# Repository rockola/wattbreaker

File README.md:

wattbreaker
================

Another silly dual-stage overdrive by Mark Hammer. 
See https://www.diystompboxes.com/smfforum/index.php?topic=126135.0 for more info.

* v0.1: initial revision, unverified

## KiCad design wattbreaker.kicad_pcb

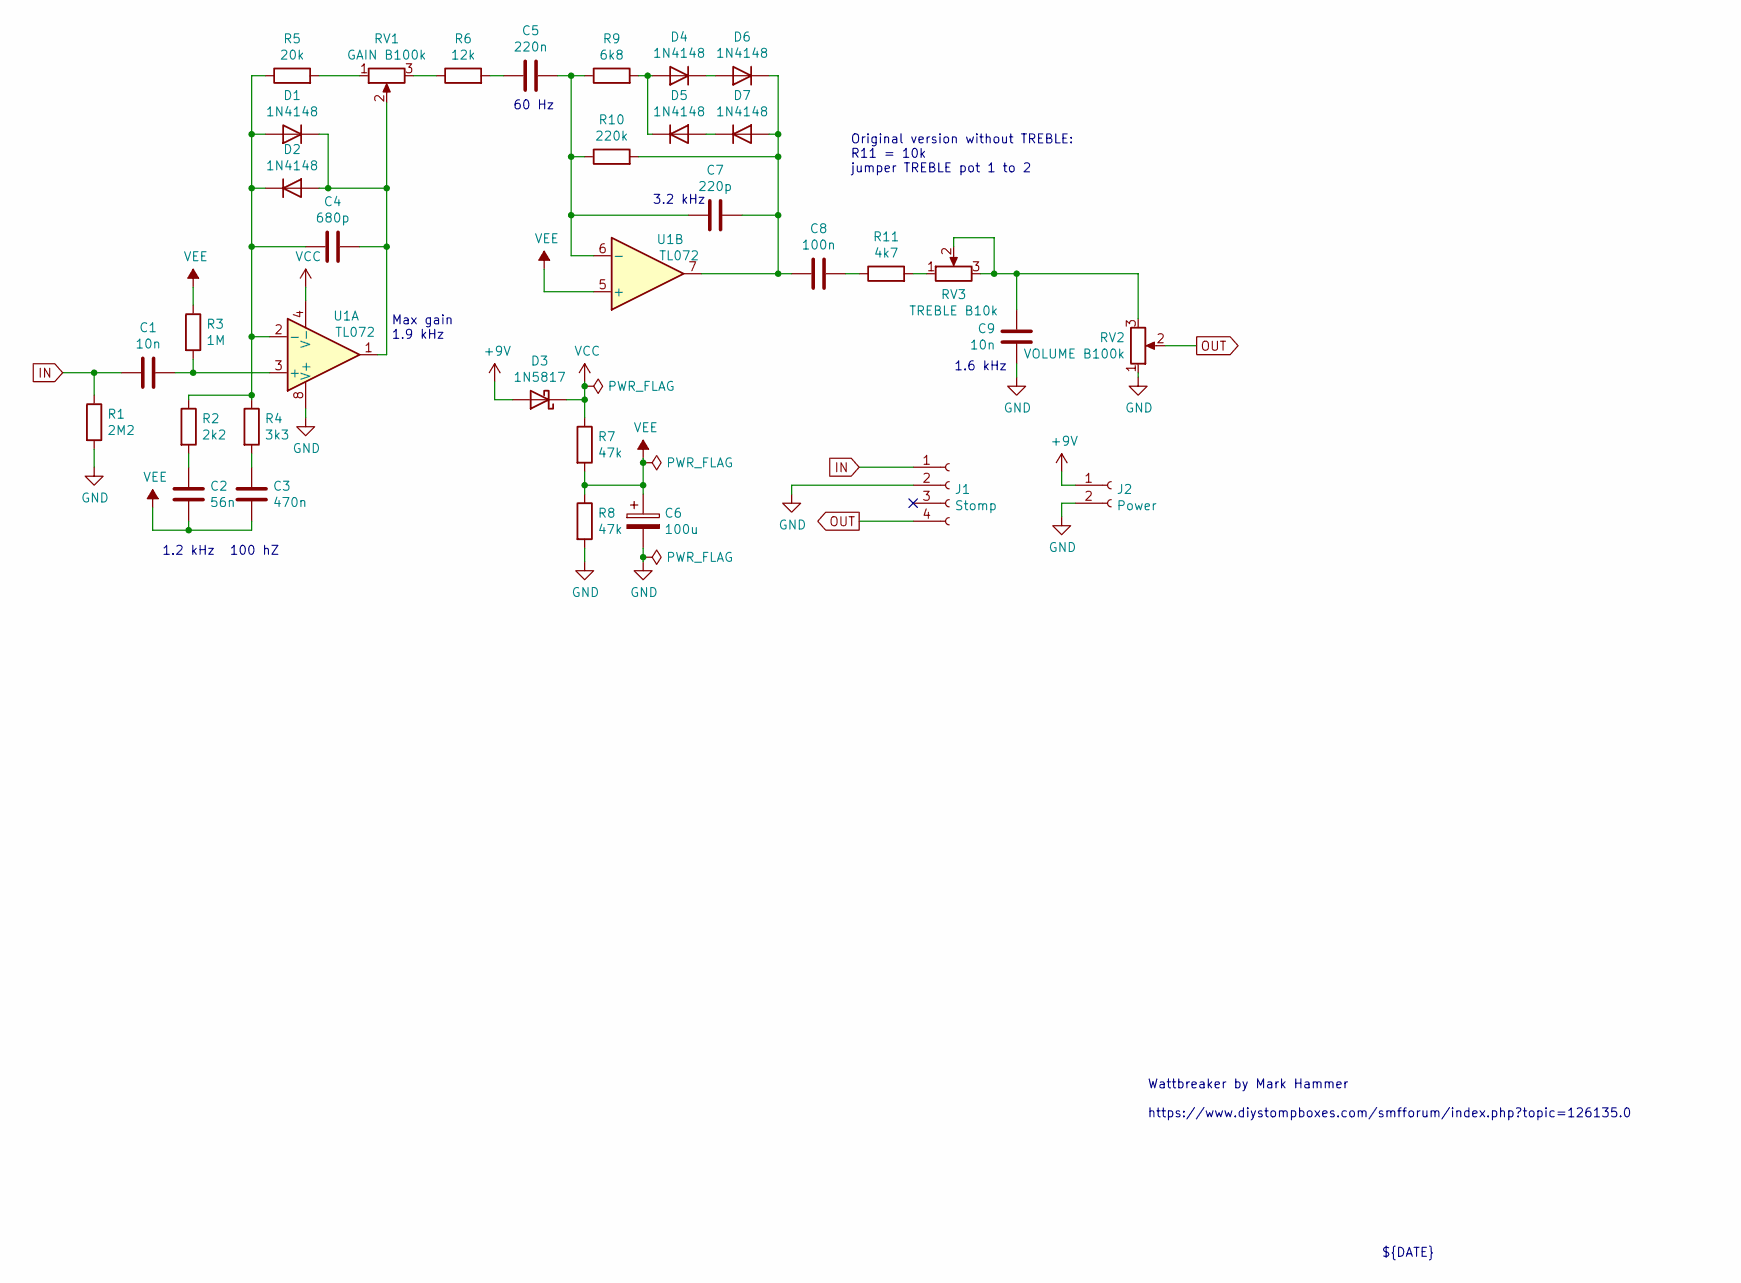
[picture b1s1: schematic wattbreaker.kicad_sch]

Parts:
C1, C9: 10n; C_Box_7.2_2.5
C2: 56n; C_Box_7.2_2.5
C3: 470n; C_Box_7.2_4.5
C4: 680p; C_Box_7.2_2.5
C5: 220n; C_Box_7.2_4.5
C6: 100u; CP_D6.3_P2.50
C7: 220p; C_Box_7.2_2.5
C8: 100n; C_Box_7.2_2.5
D1, D2, D4, D5, D6, D7: 1N4148; D_DO-35_SOD27_P7.62mm_Horizontal
D3: 1N5817; D_DO-41_SOD81_P10.16mm_Horizontal
J1: Stomp; Stomp_4pin
J2: Power; Power_Header_2pin
R1: 2M2; R_DIN0207
R2: 2k2; R_DIN0207
R3: 1M; R_DIN0207
R4: 3k3; R_DIN0207
R5: 20k; R_DIN0207
R6: 12k; R_DIN0207
R7, R8: 47k; R_DIN0207
R9: 6k8; R_DIN0207
R10: 220k; R_DIN0207
R11: 4k7; R_DIN0207
RV1: GAIN B100k; 16mm_BoardMount
RV2: VOLUME B100k; 16mm_BoardMount
RV3: TREBLE B10k; 16mm_BoardMount
U1: TL072; DIP-8_W7.62mm_Socket

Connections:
+9V: D3.2 (A), J2.1
GND: C6.2, C9.2, J1.2, J2.2, R1.2, R8.2, RV2.1, U1.8 (V+)
IN: C1.1, J1.1, R1.1
unnamed: C1.2, R3.2, U1.3 (+)
unnamed: C2.1, R2.2
unnamed: C3.1, R4.2
unnamed: C4.1, D1.2 (A), D2.1 (K), R2.1, R4.1, R5.1, U1.2 (-)
unnamed: C4.2, D1.1 (K), D2.2 (A), RV1.2, U1.1
unnamed: C5.1, R6.2
unnamed: C5.2, C7.1, R9.1, R10.1, U1.6 (-)
unnamed: C7.2, C8.1, D6.1 (K), D7.2 (A), R10.2, U1.7
unnamed: C8.2, R11.1
unnamed: C9.1, RV2.3, RV3.2, RV3.3
unnamed: D4.1 (K), D6.2 (A)
unnamed: D4.2 (A), D5.1 (K), R9.2
unnamed: D5.2 (A), D7.1 (K)
unnamed: R5.2, RV1.1
unnamed: R6.1, RV1.3
unnamed: R11.2, RV3.1
OUT: J1.4, RV2.2
VCC: D3.1 (K), R7.1, U1.4 (V-)
VEE: C2.2, C3.2, C6.1, R3.1, R7.2, R8.1, U1.5 (+)
no_connect_23: J1.3

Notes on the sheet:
Original version without TREBLE: R11 = 10k jumper TREBLE pot 1 to 2
Wattbreaker by Mark Hammer https://www.diystompboxes.com/smfforum/index.php?topic=126135.0
${DATE}
${TITLE}
60 Hz
Max gain 1.9 kHz
3.2 kHz
1.2 kHz
1.6 kHz
100 hZ
${REVISION}

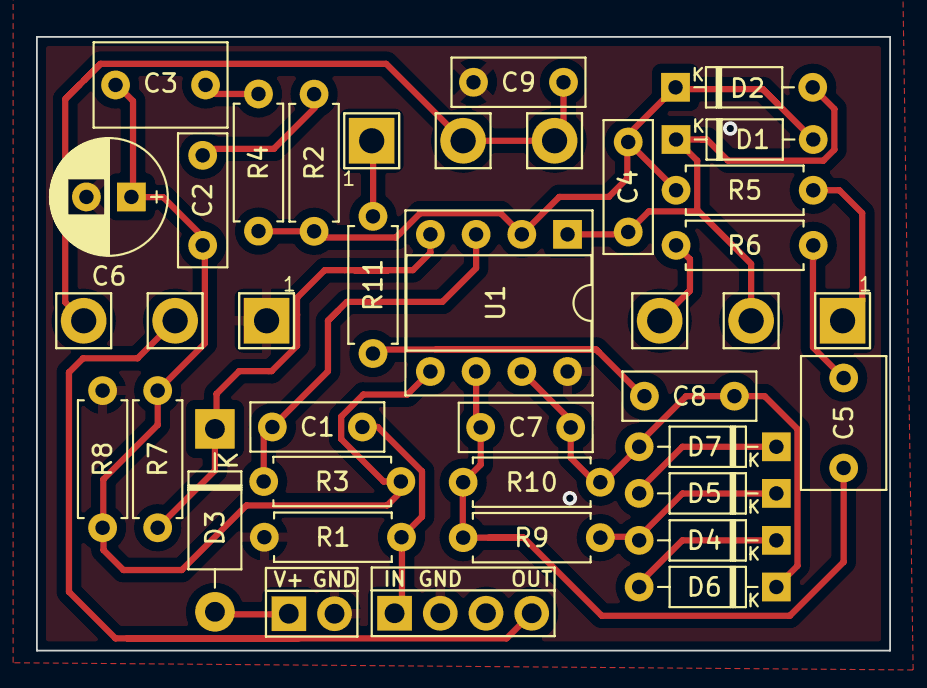
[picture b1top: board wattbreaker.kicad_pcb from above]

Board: 2 copper layers, 47.4 x 34.1 mm, 33 parts (0 on the bottom side), 22 nets.

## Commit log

2021-01-07 initial
2021-01-08 v0.1: initial revision
2021-01-08 schematic image
2021-01-08 initial README
2021-01-08 fixed image URLs
2022-01-11 updated to KiCad 6.0
